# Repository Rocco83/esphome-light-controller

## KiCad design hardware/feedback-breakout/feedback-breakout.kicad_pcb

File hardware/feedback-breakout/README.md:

This board has been never produced
Date: 20261022

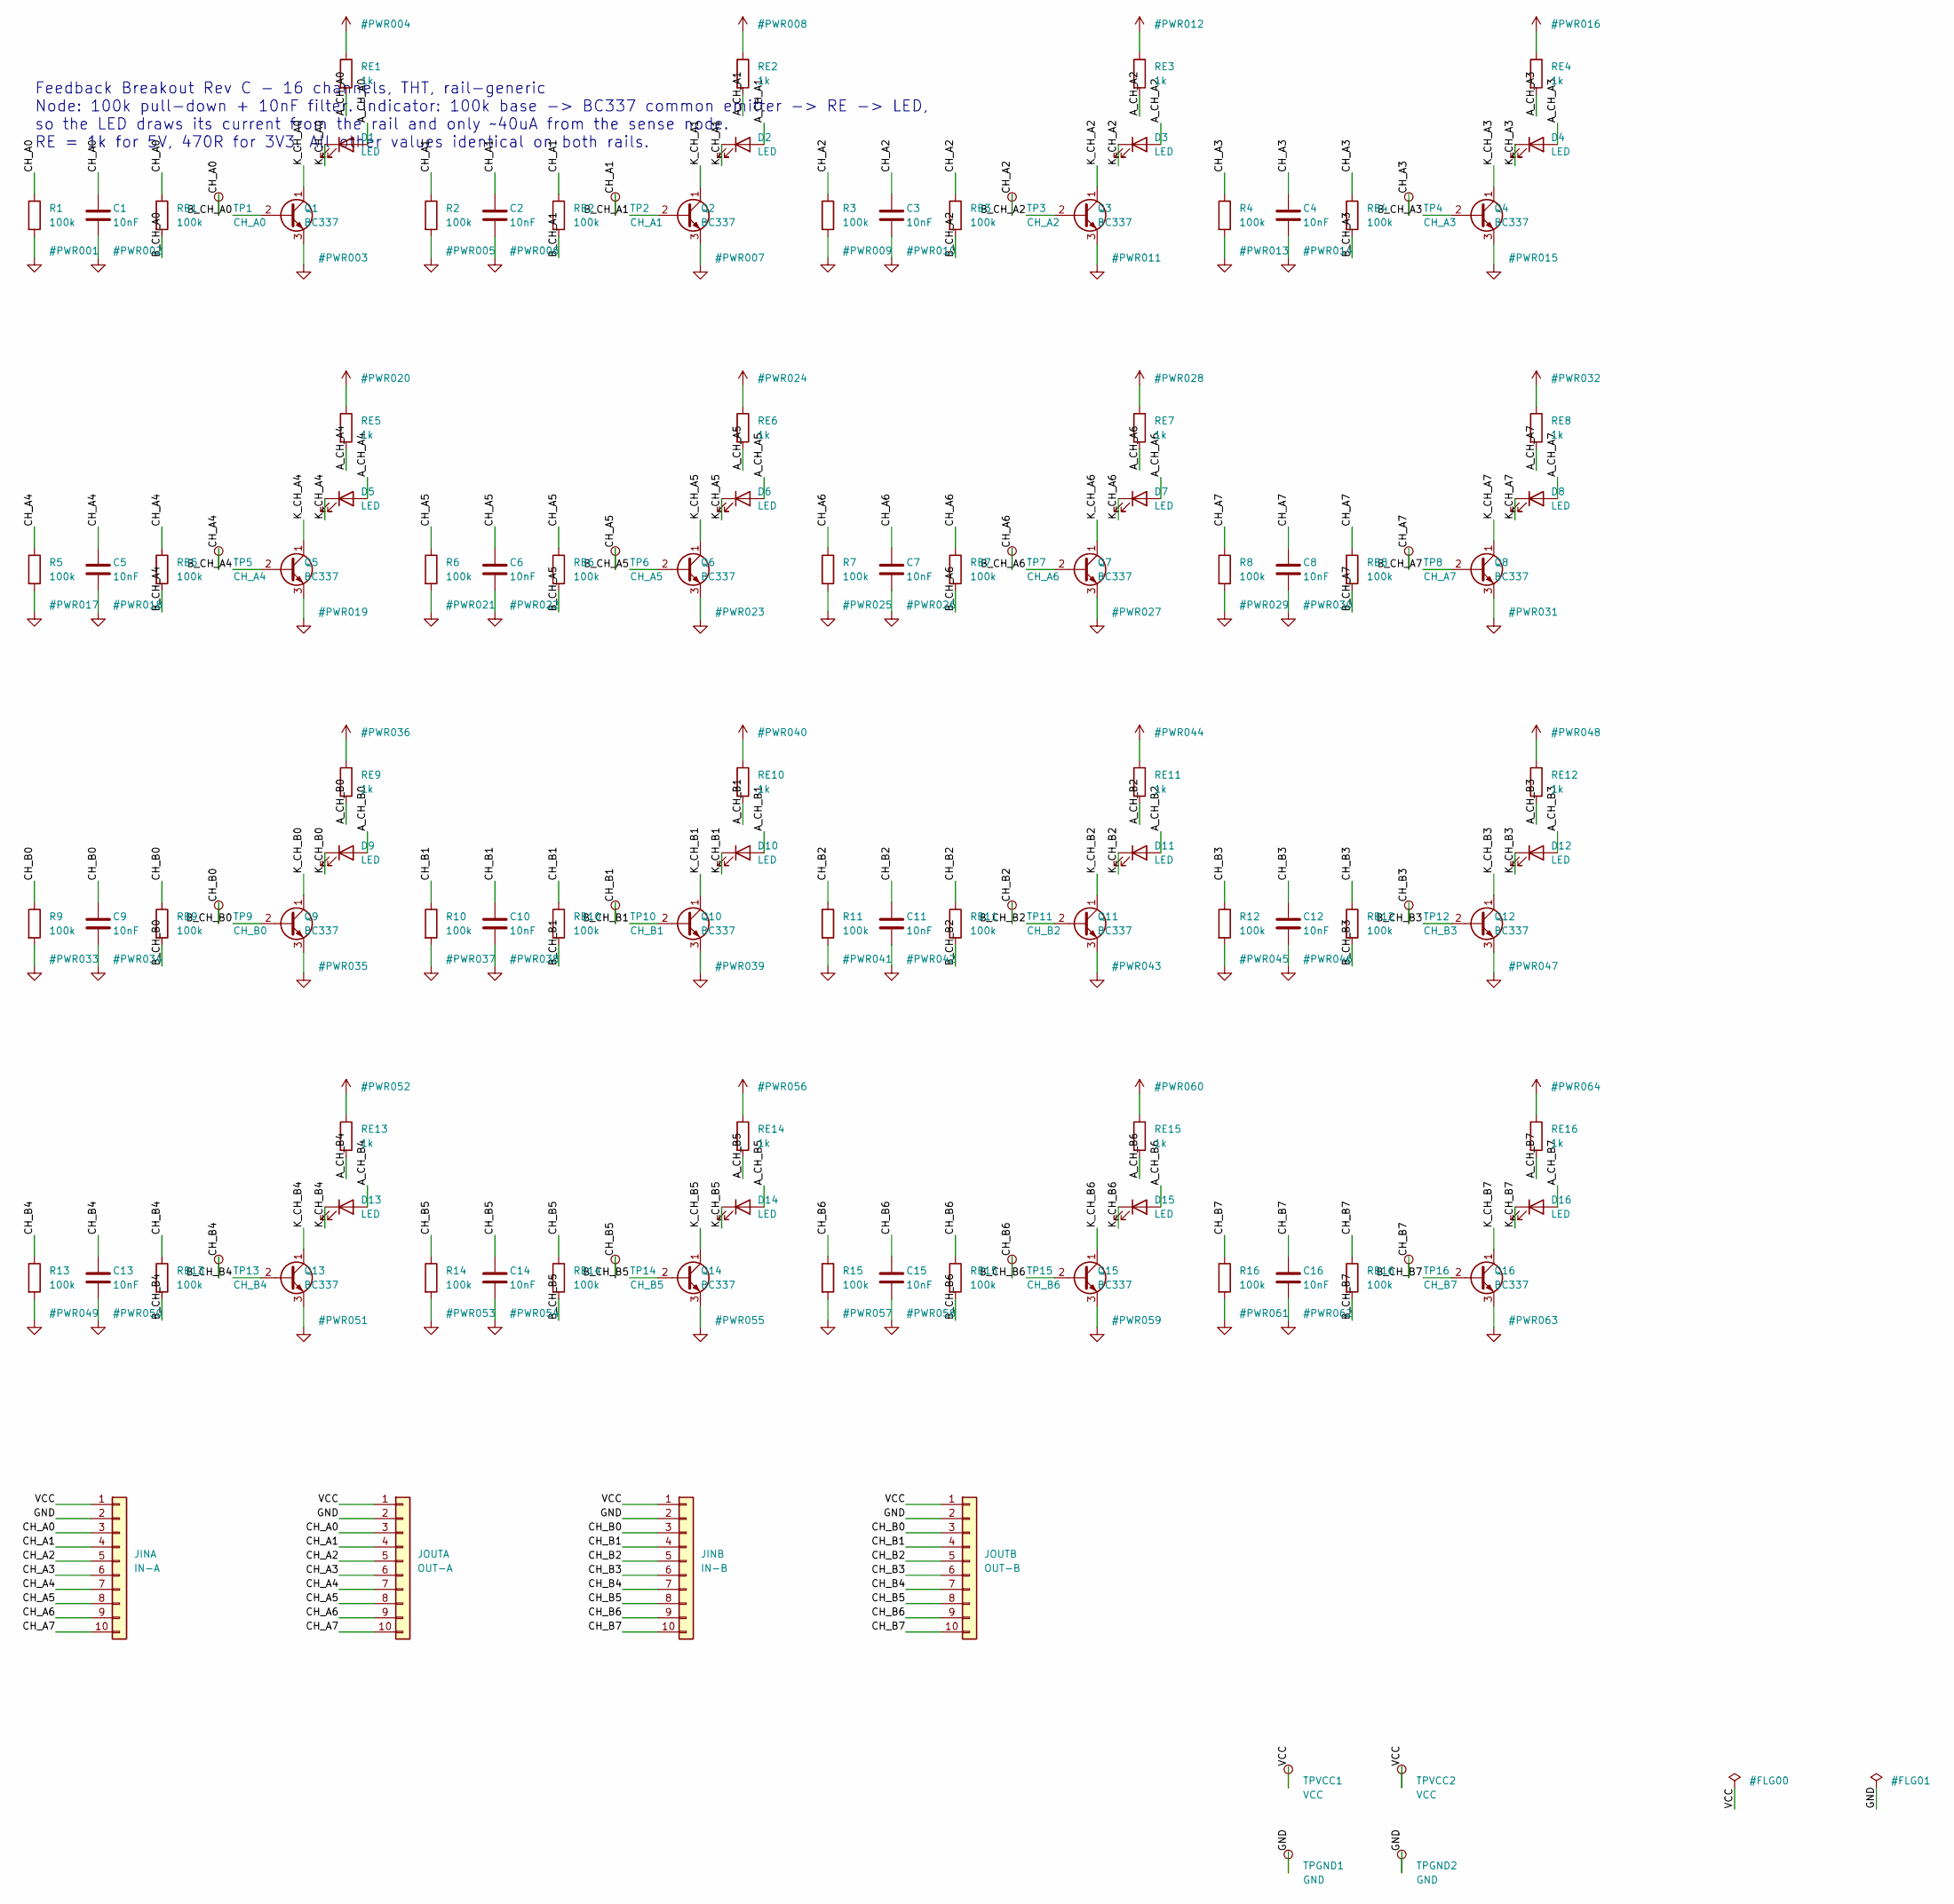
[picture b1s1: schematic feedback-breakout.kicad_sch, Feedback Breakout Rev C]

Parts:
C1, C2, C3, C4, C5, C6, C7, C8, C9, C10, C11, C12, C13, C14, C15, C16: 10nF; C_Disc_D3.0mm_W1.6mm_P2.50mm
D1, D2, D3, D4, D5, D6, D7, D8, D9, D10, D11, D12, D13, D14, D15, D16: LED; LED_D1.8mm_W3.3mm_H2.4mm
JINA: IN-A; PinHeader_1x10_P2.54mm_Vertical
JINB: IN-B; PinHeader_1x10_P2.54mm_Vertical
JOUTA: OUT-A; PinHeader_1x10_P2.54mm_Vertical
JOUTB: OUT-B; PinHeader_1x10_P2.54mm_Vertical
Q1, Q2, Q3, Q4, Q5, Q6, Q7, Q8, Q9, Q10, Q11, Q12, Q13, Q14, Q15, Q16: BC337; TO-92_Inline
R1, R2, R3, R4, R5, R6, R7, R8, R9, R10, R11, R12, R13, R14, R15, R16: 100k; R_Axial_DIN0204_L3.6mm_D1.6mm_P2.54mm_Vertical
RB1, RB2, RB3, RB4, RB5, RB6, RB7, RB8, RB9, RB10, RB11, RB12, RB13, RB14, RB15, RB16: 100k; R_Axial_DIN0204_L3.6mm_D1.6mm_P2.54mm_Vertical
RE1, RE2, RE3, RE4, RE5, RE6, RE7, RE8, RE9, RE10, RE11, RE12, RE13, RE14, RE15, RE16: 1k; R_Axial_DIN0204_L3.6mm_D1.6mm_P2.54mm_Vertical
TP1: CH_A0; TestPoint_THTPad_D1.5mm_Drill0.7mm
TP2: CH_A1; TestPoint_THTPad_D1.5mm_Drill0.7mm
TP3: CH_A2; TestPoint_THTPad_D1.5mm_Drill0.7mm
TP4: CH_A3; TestPoint_THTPad_D1.5mm_Drill0.7mm
TP5: CH_A4; TestPoint_THTPad_D1.5mm_Drill0.7mm
TP6: CH_A5; TestPoint_THTPad_D1.5mm_Drill0.7mm
TP7: CH_A6; TestPoint_THTPad_D1.5mm_Drill0.7mm
TP8: CH_A7; TestPoint_THTPad_D1.5mm_Drill0.7mm
TP9: CH_B0; TestPoint_THTPad_D1.5mm_Drill0.7mm
TP10: CH_B1; TestPoint_THTPad_D1.5mm_Drill0.7mm
TP11: CH_B2; TestPoint_THTPad_D1.5mm_Drill0.7mm
TP12: CH_B3; TestPoint_THTPad_D1.5mm_Drill0.7mm
TP13: CH_B4; TestPoint_THTPad_D1.5mm_Drill0.7mm
TP14: CH_B5; TestPoint_THTPad_D1.5mm_Drill0.7mm
TP15: CH_B6; TestPoint_THTPad_D1.5mm_Drill0.7mm
TP16: CH_B7; TestPoint_THTPad_D1.5mm_Drill0.7mm
TPGND1, TPGND2: GND; TestPoint_THTPad_D1.5mm_Drill0.7mm
TPVCC1, TPVCC2: VCC; TestPoint_THTPad_D1.5mm_Drill0.7mm

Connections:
A_CH_A0: D1.2 (A), RE1.2
A_CH_A1: D2.2 (A), RE2.2
A_CH_A2: D3.2 (A), RE3.2
A_CH_A3: D4.2 (A), RE4.2
A_CH_A4: D5.2 (A), RE5.2
A_CH_A5: D6.2 (A), RE6.2
A_CH_A6: D7.2 (A), RE7.2
A_CH_A7: D8.2 (A), RE8.2
A_CH_B0: D9.2 (A), RE9.2
A_CH_B1: D10.2 (A), RE10.2
A_CH_B2: D11.2 (A), RE11.2
A_CH_B3: D12.2 (A), RE12.2
A_CH_B4: D13.2 (A), RE13.2
A_CH_B5: D14.2 (A), RE14.2
A_CH_B6: D15.2 (A), RE15.2
A_CH_B7: D16.2 (A), RE16.2
B_CH_A0: Q1.2 (B), RB1.2
B_CH_A1: Q2.2 (B), RB2.2
B_CH_A2: Q3.2 (B), RB3.2
B_CH_A3: Q4.2 (B), RB4.2
B_CH_A4: Q5.2 (B), RB5.2
B_CH_A5: Q6.2 (B), RB6.2
B_CH_A6: Q7.2 (B), RB7.2
B_CH_A7: Q8.2 (B), RB8.2
B_CH_B0: Q9.2 (B), RB9.2
B_CH_B1: Q10.2 (B), RB10.2
B_CH_B2: Q11.2 (B), RB11.2
B_CH_B3: Q12.2 (B), RB12.2
B_CH_B4: Q13.2 (B), RB13.2
B_CH_B5: Q14.2 (B), RB14.2
B_CH_B6: Q15.2 (B), RB15.2
B_CH_B7: Q16.2 (B), RB16.2
CH_A0: C1.1, JINA.3, JOUTA.3, R1.1, RB1.1, TP1.1
CH_A1: C2.1, JINA.4, JOUTA.4, R2.1, RB2.1, TP2.1
CH_A2: C3.1, JINA.5, JOUTA.5, R3.1, RB3.1, TP3.1
CH_A3: C4.1, JINA.6, JOUTA.6, R4.1, RB4.1, TP4.1
CH_A4: C5.1, JINA.7, JOUTA.7, R5.1, RB5.1, TP5.1
CH_A5: C6.1, JINA.8, JOUTA.8, R6.1, RB6.1, TP6.1
CH_A6: C7.1, JINA.9, JOUTA.9, R7.1, RB7.1, TP7.1
CH_A7: C8.1, JINA.10, JOUTA.10, R8.1, RB8.1, TP8.1
CH_B0: C9.1, JINB.3, JOUTB.3, R9.1, RB9.1, TP9.1
CH_B1: C10.1, JINB.4, JOUTB.4, R10.1, RB10.1, TP10.1
CH_B2: C11.1, JINB.5, JOUTB.5, R11.1, RB11.1, TP11.1
CH_B3: C12.1, JINB.6, JOUTB.6, R12.1, RB12.1, TP12.1
CH_B4: C13.1, JINB.7, JOUTB.7, R13.1, RB13.1, TP13.1
CH_B5: C14.1, JINB.8, JOUTB.8, R14.1, RB14.1, TP14.1
CH_B6: C15.1, JINB.9, JOUTB.9, R15.1, RB15.1, TP15.1
CH_B7: C16.1, JINB.10, JOUTB.10, R16.1, RB16.1, TP16.1
GND: C1.2, C2.2, C3.2, C4.2, C5.2, C6.2, C7.2, C8.2, C9.2, C10.2, C11.2, C12.2, C13.2, C14.2, C15.2, C16.2, JINA.2, JINB.2, JOUTA.2, JOUTB.2, Q1.3 (E), Q2.3 (E), Q3.3 (E), Q4.3 (E), Q5.3 (E), Q6.3 (E), Q7.3 (E), Q8.3 (E), Q9.3 (E), Q10.3 (E), Q11.3 (E), Q12.3 (E), Q13.3 (E), Q14.3 (E), Q15.3 (E), Q16.3 (E), R1.2, R2.2, R3.2, R4.2, R5.2, R6.2, R7.2, R8.2, R9.2, R10.2, R11.2, R12.2, R13.2, R14.2, R15.2, R16.2, TPGND1.1, TPGND2.1
K_CH_A0: D1.1 (K), Q1.1 (C)
K_CH_A1: D2.1 (K), Q2.1 (C)
K_CH_A2: D3.1 (K), Q3.1 (C)
K_CH_A3: D4.1 (K), Q4.1 (C)
K_CH_A4: D5.1 (K), Q5.1 (C)
K_CH_A5: D6.1 (K), Q6.1 (C)
K_CH_A6: D7.1 (K), Q7.1 (C)
K_CH_A7: D8.1 (K), Q8.1 (C)
K_CH_B0: D9.1 (K), Q9.1 (C)
K_CH_B1: D10.1 (K), Q10.1 (C)
K_CH_B2: D11.1 (K), Q11.1 (C)
K_CH_B3: D12.1 (K), Q12.1 (C)
K_CH_B4: D13.1 (K), Q13.1 (C)
K_CH_B5: D14.1 (K), Q14.1 (C)
K_CH_B6: D15.1 (K), Q15.1 (C)
K_CH_B7: D16.1 (K), Q16.1 (C)
VCC: JINA.1, JINB.1, JOUTA.1, JOUTB.1, RE1.1, RE2.1, RE3.1, RE4.1, RE5.1, RE6.1, RE7.1, RE8.1, RE9.1, RE10.1, RE11.1, RE12.1, RE13.1, RE14.1, RE15.1, RE16.1, TPVCC1.1, TPVCC2.1

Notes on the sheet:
Feedback Breakout Rev C - 16 channels, THT, rail-generic Node: 100k pull-down + 10nF filter. Indicator: 100k base -> BC337 common emitter -> RE -> LED, so the LED draws its current from the rail and only ~40uA from the sense node. RE = 1k for 5V, 470R for 3V3. All other values identical on both rai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

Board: 2 copper layers, 122 parts (0 on the bottom side), 66 nets, no tracks yet.

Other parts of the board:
H1, H2: M3; MountingHole_3.2mm_M3_DIN965

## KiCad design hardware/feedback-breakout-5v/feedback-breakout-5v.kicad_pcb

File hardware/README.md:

# Feedback Breakout Rev C

KiCad 9 projects for the 16-channel input feedback conditioning board — the manufactured
replacement for the hand-soldered perfboard between the H11AA1 optoisolator boards and the
MCP23017 expanders.

| Directory | Build | Board | Notes |
|---|---|---|---|
| `feedback-breakout/` | through-hole | 160 × 34 mm | uses the parts already on hand |
| `feedback-breakout-smd/` | 0805 / SOT-23 | 130 × 26 mm | green LEDs only; `bom.csv` + `cpl.csv` for an assembled quote |

Both are built entirely from stock KiCad 9 libraries and carry their own `sym-lib-table` /
`fp-lib-table`, so they open without depending on a global symbol table.

## Where this board sits

```
   12 V field side                              5 V logic side (opto board)
RET+12_SIGn ─[2K7]─[RED]─┐                  ┌──────── +5V
                      H11AA1 ───────────────┤ emitter
GND_SIG ─────────────────┘                  │
                                       DIGn ─┬─ [10K] ── GND
                                             ├─ BC337 ─[680]─[GRN]
                                             │
                                       ~10 m of small-gauge wire
                                             │
                          THIS BOARD ────────┼─ [100k] ─────────── GND   fail-safe level
                                             ├─ [10nF] ─────────── GND   line filter
                                             ├─ [100k] ─ Q base          indicator driver
                                             ├─ test pad
                                             └─ MCP23017 input

                          indicator:  VCC ─[RE]─[LED]─ collector, emitter ─ GND
```

## Why the indicator uses a transistor

The H11AA1 output is an emitter follower — a *current* source limited by LED drive × CTR, not a
stiff voltage source. From the opto board's Eagle design: 3.24 mA through the opto LED, and at the
datasheet minimum CTR of 20 % that leaves **0.66 mA** available at the node.

| Branch | Old perfboard | LED direct | **This board** |
|---|---:|---:|---:|
| Opto board 10k pull-down | 0.470 | 0.470 | 0.470 |
| Opto board BC337 base | 0.014 | 0.014 | 0.014 |
| This board's pull-down | 0.470 (10k) | 0.047 (100k) | 0.047 (100k) |
| This board's LED branch | — | 0.368 | **0.040** |
| MCP23017 input | 0.001 | 0.001 | 0.001 |
| **Total drawn from the node** | **0.955 mA** | **0.900 mA** | **0.572 mA** |
| vs 0.66 mA available | over | over | **fits** |

A common-emitter stage takes its LED current from the rail through the collector and only ~40 µA
of base current from the node. That is what allows an indicator *and* a lower node load than the
board has today.

The opto board's own BC337 cannot serve this purpose: its emitter goes straight to its own LED and
never reaches the connector, and it is 10 m away. A follower buffers where it sits.

> **Note.** Today's board is already over budget at 0.955 mA against a worst-case 0.66 mA — a
> plausible cause of the one channel that reads stuck LOW. The 0.66 mA figure uses the datasheet
> minimum CTR at I<sub>F</sub> = 10 mA while these optos run at 3.3 mA, where it is unspecified;
> real parts are usually better, which is why 15 of 16 channels work today. Use the test pads to
> measure the node against the 4.0 V threshold.

## Rail-generic

A common emitter sets the LED current from the rail, not from the node, so the same board works on
either rail with one value change:

| Rail | RB | RE | LED current | Base current |
|---|---|---|---:|---:|
| 5 V | 100k | **1k** | 2.60 mA | 40 µA |
| 3.3 V | 100k | **470R** | 1.91 mA | 23 µA |

An emitter *follower* would not survive this: at 3.3 V its emitter reaches only 2.3 V against a
2.2 V green LED. Note also that **blue LEDs (Vf ≈ 3.1 V) will not light on a 3.3 V rail at all**,
and at 5 V they run dimmer than green for the same RE.

## No ground pour

GND is an ordinary 54-pad net on both boards — **no zones, no stitching vias** — to be routed by
hand. This is deliberate. The two mechanisms a pour would help do not apply at this scale:

| | |
|---|---|
| Filter integrity | The node sees a 9.09 kΩ source (100k ∥ the opto board's 10k) into 10 nF, cutoff 1.75 kHz. A 160 mm return track is ~160 nH → **0.002 Ω at the cutoff**, 0.00002 % of the source impedance. Even at 100 MHz it is 1.1 %. |
| Shared-impedance offset | All 16 LEDs lit is 41.6 mA through ~80 mΩ of 1 mm track → **3.3 mV**, 0.08 % of the 4.0 V threshold. |

The usual reasons for a plane are absent too: no ns-edge digital (state changes at human speed,
100 ms poll), no µV analog, no radiated-emissions requirement, and no surge role — the H11AA1
provides galvanic isolation.

The trade-off, accepted knowingly: removing the pour *adds* routing work rather than removing it.
GND is the largest net on the board at 54 pads.

## Specification

- 2 layer, 1.6 mm, all through-hole (or 0805/SOT-23 for the SMD variant)
- **Mounting** 2 × M3, ⌀3.2 mm non-plated, **68.58 mm apart, centred both axes**
- **Connectors** 4 × 1×10, 2.54 mm — `JINA`/`JINB` on the top edge, `JOUTA`/`JOUTB` on the bottom,
  banks side by side so each channel's IN and OUT pins are vertically aligned
- **Per channel** 100k pull-down, 10 nF filter, 100k base resistor, transistor, RE, LED, test pad
- **Test points** 16 channel pads plus VCC and GND pads at each end
- **120 footprints**, 66 nets

### Header pinout — all four identical

| Pin | Net |
|---:|---|
| 1 | VCC |
| 2 | GND |
| 3–10 | CH0–CH7 of that bank |

`J*A` → MCP23017 GPA0–7, `J*B` → GPB0–7.

### Parts

| Ref | Value | THT footprint | SMD footprint |
|---|---|---|---|
| R, RB | 100k | `R_Axial_DIN0204_L3.6mm_D1.6mm_P2.54mm_Vertical` | `R_0805_2012Metric` |
| RE | 1k (5 V) / 470R (3V3) | same | same |
| C | 10 nF | `C_Disc_D3.0mm_W1.6mm_P2.50mm` | `C_0805_2012Metric` |
| Q | BC337 (C-B-E) / **BC817-40 (B-E-C)** | `TO-92_Inline` | `SOT-23` |
| D | green LED | `LED_D1.8mm_W3.3mm_H2.4mm` | `LED_0805_2012Metric` |
| TP | — | `TestPoint_THTPad_D1.5mm_Drill0.7mm` | same |
| J | 1×10 | `PinHeader_1x10_P2.54mm_Vertical` | same |

**The transistor pinout differs between the two builds** — BC337 in TO-92 is C-B-E, BC817 in
SOT-23 is B-E-C. The boards wire them accordingly; do not cross-substitute.

The THT resistor footprint suits both a generic 1/6 W (3.2 × 1.8 mm) and the TE CFR16 series
(3.5 × 1.85 mm, 0.25 W) — interchangeable here, both mounted **vertically**. A 6.3 mm DIN0207 body
will *not* fit. Dissipation is under 1.2 mW worst case, so 1/6 W has ~145× margin.

Reference designators are on F.Fab, not silkscreen — no room at this density. The rail-dependent
value is called out on both silkscreen layers.

## BOM for 2 boards

| Part | Qty | |
|---|---:|---|
| 100k (R + RB) | 64 | |
| **1k (RE)** | **32** | needed for the 5 V build |
| 10 nF | 32 | |
| BC337 / BC817-40 | 32 | |
| green LED | 32 | |
| 1×10 header | 8 | |

For the SMD variant, `bom.csv` and `cpl.csv` are in the format an assembly house expects:
**96 SMD placements per board across 5 unique parts**, with the 4 headers and 20 test pads left
as hand-soldered through-hole.

## Status

| Check | THT | SMD |
|---|---|---|
| `kicad-cli sch erc` | **0 violations** | **0 violations** |
| Schematic ↔ PCB netlist | **identical**, 66 nets | **identical**, 66 nets |
| Every `CH_*` net | 6 nodes (JIN, JOUT, R, C, RB, TP) | same |
| `kicad-cli pcb drc` | 15 violations | 21 violations |
| Unconnected | 202 | 202 |

**Open items, both deliberate:**

1. **The M3 holes overlap four channels** — 3, 4, 11, 12 on the THT board and 2, 3, 11, 12 on the
   SMD one. At 68.58 mm spacing they land inside the component band; the spacing was kept to match
   the existing standoffs, and the placement around them is to be adjusted by hand. Every DRC
   violation names `H1`, `H2`, or one of the parts sitting on them.
2. **Not routed.** The 202 unconnected items are the ratsnest, including the 53 GND connections.

## Connector plating

At ~0.57 mA these are dry-circuit contacts, far below the ~10 mA that reliably breaks through oxide
on tin plating — the regime where fretting corrosion appears as intermittent, channel-specific
faults, which is what the seven stuck-high channels looked like. Specify **gold-plated** contacts on
both the header and the mating connector.

## Source hardware

Values above are read from the Eagle project for the optoisolator board (`LightRetaggioSchema`,
2020-04-23): 8 channels, H11AA1 AC-input optocouplers, 2K7 field resistors, 10K pull-downs,
BC337 + 680R LED drivers, manual test buttons SW1–SW8, and no capacitors anywhere on the board.

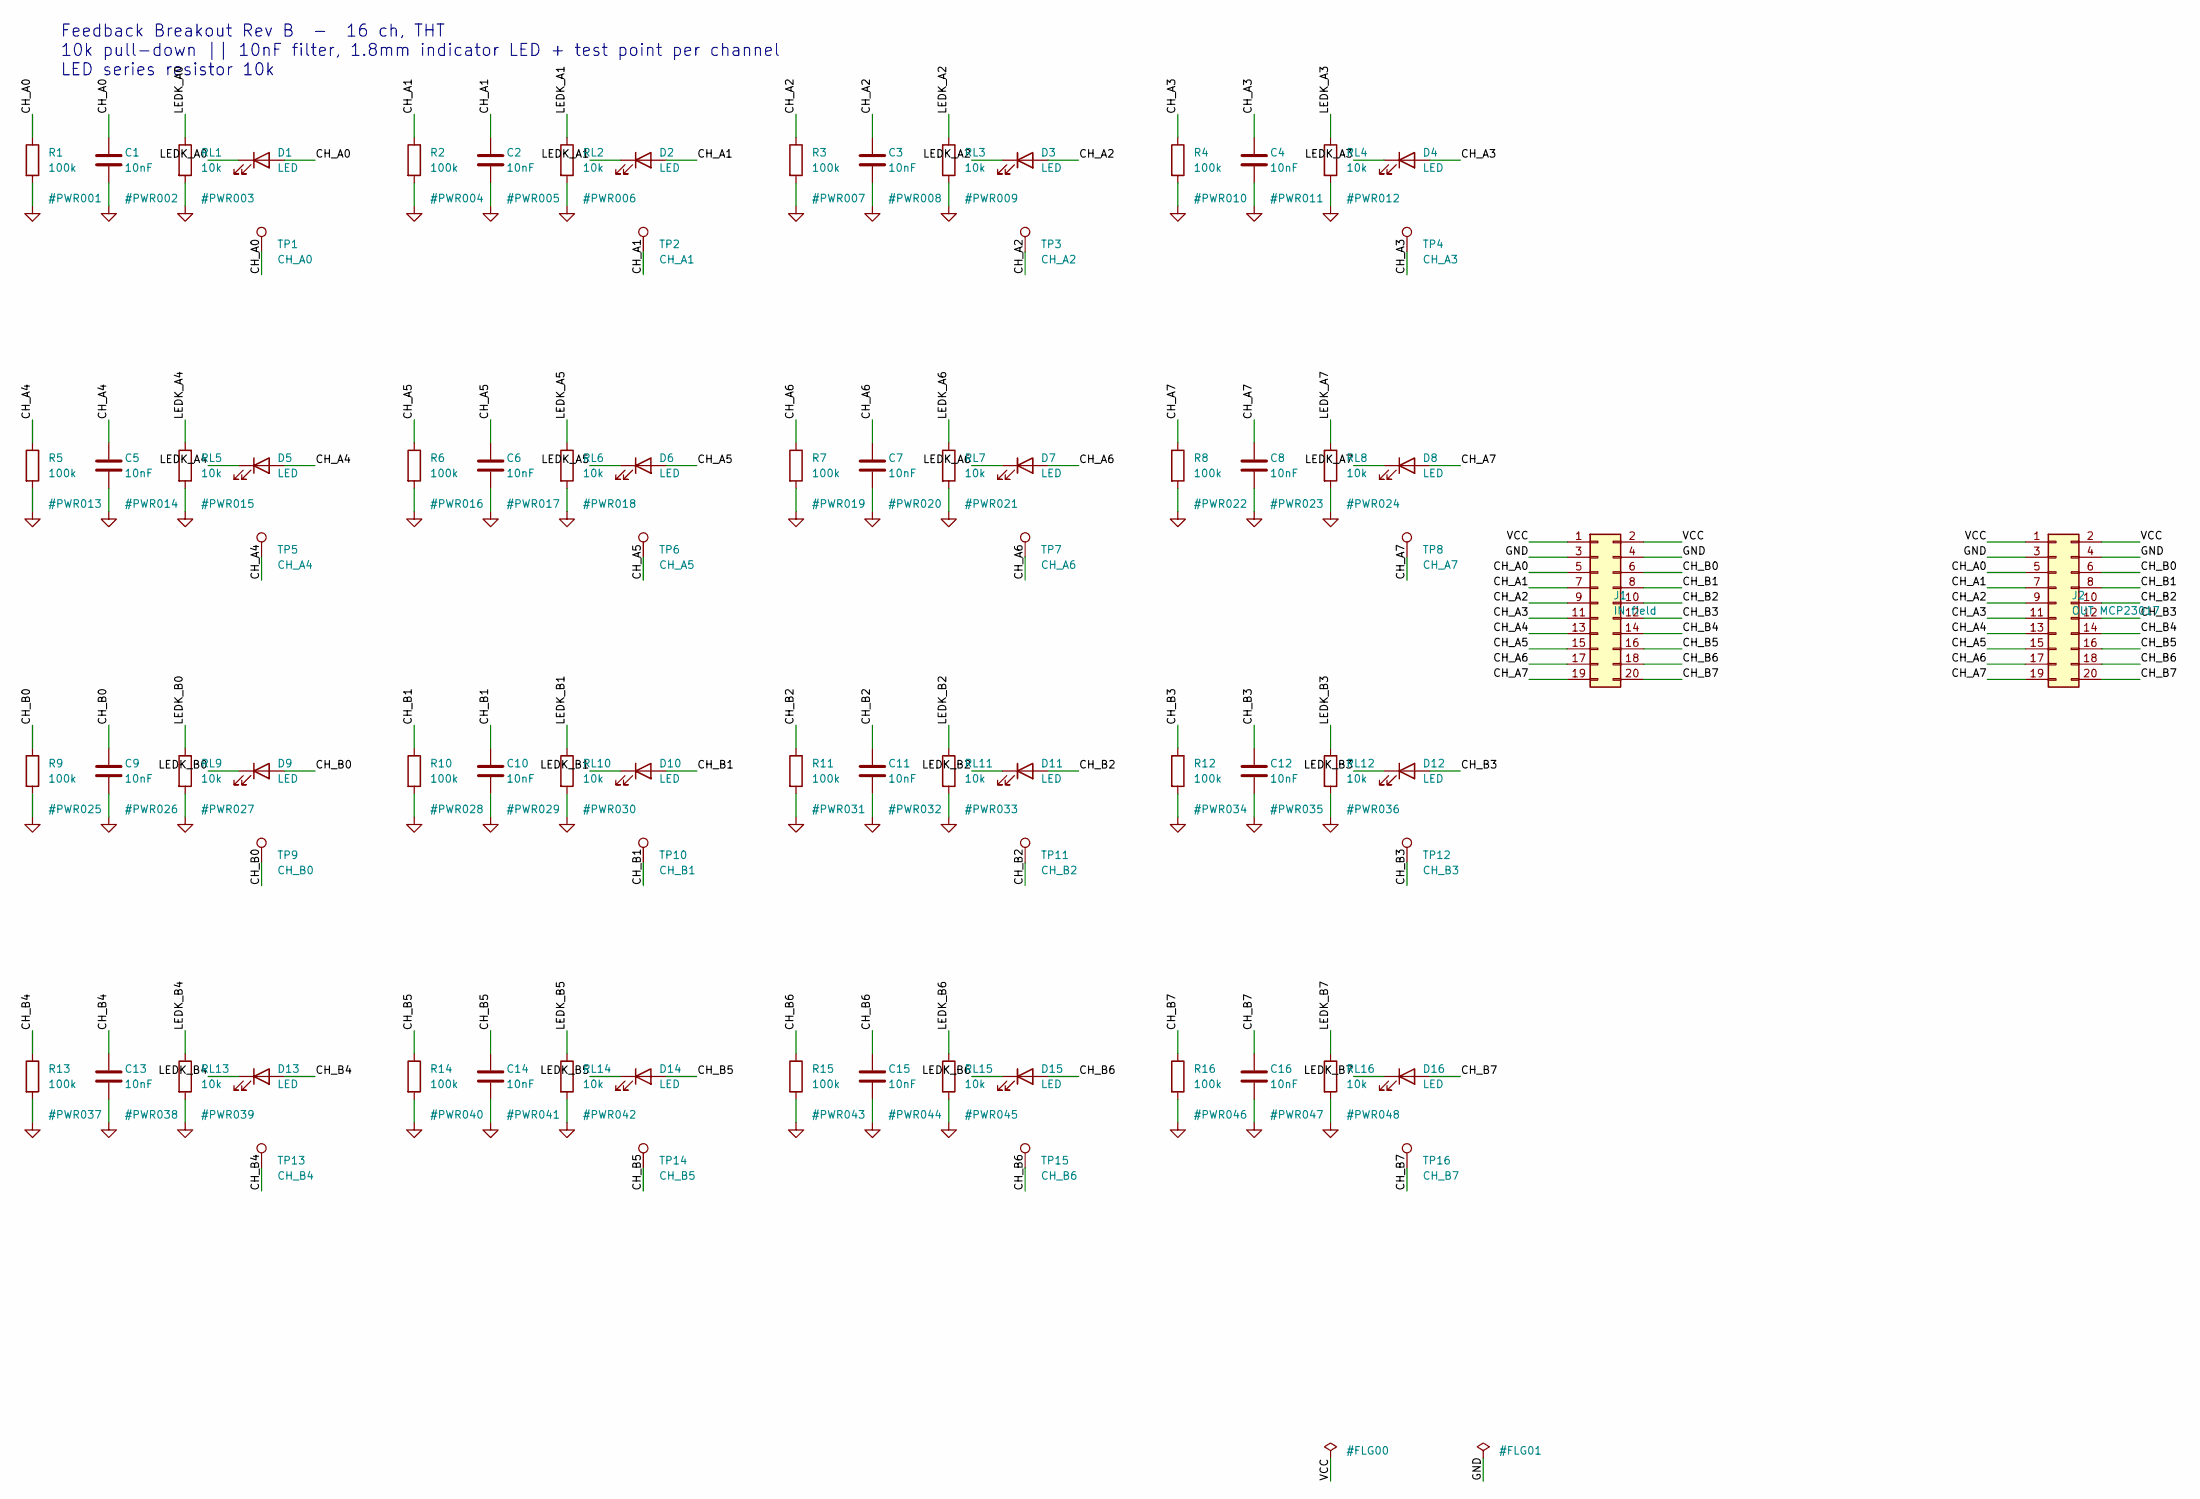
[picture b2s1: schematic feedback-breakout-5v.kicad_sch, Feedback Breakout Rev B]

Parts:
C1, C2, C3, C4, C5, C6, C7, C8, C9, C10, C11, C12, C13, C14, C15, C16: 10nF; C_Disc_D3.0mm_W1.6mm_P2.50mm
D1, D2, D3, D4, D5, D6, D7, D8, D9, D10, D11, D12, D13, D14, D15, D16: LED; LED_D1.8mm_W3.3mm_H2.4mm
J1: IN field; PinHeader_2x10_P2.54mm_Vertical
J2: OUT MCP23017; PinHeader_2x10_P2.54mm_Vertical
R1, R2, R3, R4, R5, R6, R7, R8, R9, R10, R11, R12, R13, R14, R15, R16: 100k; R_Axial_DIN0204_L3.6mm_D1.6mm_P2.54mm_Vertical
RL1, RL2, RL3, RL4, RL5, RL6, RL7, RL8, RL9, RL10, RL11, RL12, RL13, RL14, RL15, RL16: 10k; R_Axial_DIN0204_L3.6mm_D1.6mm_P2.54mm_Vertical
TP1: CH_A0; TestPoint_Pad_1.0x1.0mm
TP2: CH_A1; TestPoint_Pad_1.0x1.0mm
TP3: CH_A2; TestPoint_Pad_1.0x1.0mm
TP4: CH_A3; TestPoint_Pad_1.0x1.0mm
TP5: CH_A4; TestPoint_Pad_1.0x1.0mm
TP6: CH_A5; TestPoint_Pad_1.0x1.0mm
TP7: CH_A6; TestPoint_Pad_1.0x1.0mm
TP8: CH_A7; TestPoint_Pad_1.0x1.0mm
TP9: CH_B0; TestPoint_Pad_1.0x1.0mm
TP10: CH_B1; TestPoint_Pad_1.0x1.0mm
TP11: CH_B2; TestPoint_Pad_1.0x1.0mm
TP12: CH_B3; TestPoint_Pad_1.0x1.0mm
TP13: CH_B4; TestPoint_Pad_1.0x1.0mm
TP14: CH_B5; TestPoint_Pad_1.0x1.0mm
TP15: CH_B6; TestPoint_Pad_1.0x1.0mm
TP16: CH_B7; TestPoint_Pad_1.0x1.0mm

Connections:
CH_A0: C1.1, D1.2 (A), J1.5, J2.5, R1.1, TP1.1
CH_A1: C2.1, D2.2 (A), J1.7, J2.7, R2.1, TP2.1
CH_A2: C3.1, D3.2 (A), J1.9, J2.9, R3.1, TP3.1
CH_A3: C4.1, D4.2 (A), J1.11, J2.11, R4.1, TP4.1
CH_A4: C5.1, D5.2 (A), J1.13, J2.13, R5.1, TP5.1
CH_A5: C6.1, D6.2 (A), J1.15, J2.15, R6.1, TP6.1
CH_A6: C7.1, D7.2 (A), J1.17, J2.17, R7.1, TP7.1
CH_A7: C8.1, D8.2 (A), J1.19, J2.19, R8.1, TP8.1
CH_B0: C9.1, D9.2 (A), J1.6, J2.6, R9.1, TP9.1
CH_B1: C10.1, D10.2 (A), J1.8, J2.8, R10.1, TP10.1
CH_B2: C11.1, D11.2 (A), J1.10, J2.10, R11.1, TP11.1
CH_B3: C12.1, D12.2 (A), J1.12, J2.12, R12.1, TP12.1
CH_B4: C13.1, D13.2 (A), J1.14, J2.14, R13.1, TP13.1
CH_B5: C14.1, D14.2 (A), J1.16, J2.16, R14.1, TP14.1
CH_B6: C15.1, D15.2 (A), J1.18, J2.18, R15.1, TP15.1
CH_B7: C16.1, D16.2 (A), J1.20, J2.20, R16.1, TP16.1
GND: C1.2, C2.2, C3.2, C4.2, C5.2, C6.2, C7.2, C8.2, C9.2, C10.2, C11.2, C12.2, C13.2, C14.2, C15.2, C16.2, J1.3, J1.4, J2.3, J2.4, R1.2, R2.2, R3.2, R4.2, R5.2, R6.2, R7.2, R8.2, R9.2, R10.2, R11.2, R12.2, R13.2, R14.2, R15.2, R16.2, RL1.2, RL2.2, RL3.2, RL4.2, RL5.2, RL6.2, RL7.2, RL8.2, RL9.2, RL10.2, RL11.2, RL12.2, RL13.2, RL14.2, RL15.2, RL16.2
LEDK_A0: D1.1 (K), RL1.1
LEDK_A1: D2.1 (K), RL2.1
LEDK_A2: D3.1 (K), RL3.1
LEDK_A3: D4.1 (K), RL4.1
LEDK_A4: D5.1 (K), RL5.1
LEDK_A5: D6.1 (K), RL6.1
LEDK_A6: D7.1 (K), RL7.1
LEDK_A7: D8.1 (K), RL8.1
LEDK_B0: D9.1 (K), RL9.1
LEDK_B1: D10.1 (K), RL10.1
LEDK_B2: D11.1 (K), RL11.1
LEDK_B3: D12.1 (K), RL12.1
LEDK_B4: D13.1 (K), RL13.1
LEDK_B5: D14.1 (K), RL14.1
LEDK_B6: D15.1 (K), RL15.1
LEDK_B7: D16.1 (K), RL16.1
VCC: J1.1, J1.2, J2.1, J2.2

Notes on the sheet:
Feedback Breakout Rev B - 16 ch, THT 10k pull-down || 10nF filter, 1.8mm indicator LED + test point per channel LED series resistor 10k

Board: 2 copper layers, 84 parts (0 on the bottom side), 34 nets, no tracks yet.

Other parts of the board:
H1, H2: M3; MountingHole_3.2mm_M3_DIN965

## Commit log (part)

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2026-01-03 Still broken, added lambda, several modifications
2026-01-07 prod v0.1
    - fixed the logic of the read using a script
    - added the safe mode
    - bah, too many other things
    - still broken code
2026-01-07 0.3
    - fixed inverted output (relay when to gnd -> on)
    - fixed back the i2c bus to 400kHz
    - fixed the code to fallback the state of the light to the real state provided by the input
2026-01-07 fixed logic that sync web, added debug
2026-01-08 changed hw to i2c_state, changed to debug 10s logs
2026-02-08 Prod v1
    - Reduced the frequency of the debug logs
    - added i2c logs
    - added the PULLUP to the configuration
    - require now the resistance+capacity to manage the long line
2026-02-08 added to gitignore .platformio
